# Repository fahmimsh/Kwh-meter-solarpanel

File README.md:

# Kwh-meter-solarpanel

STM32F103C8T6

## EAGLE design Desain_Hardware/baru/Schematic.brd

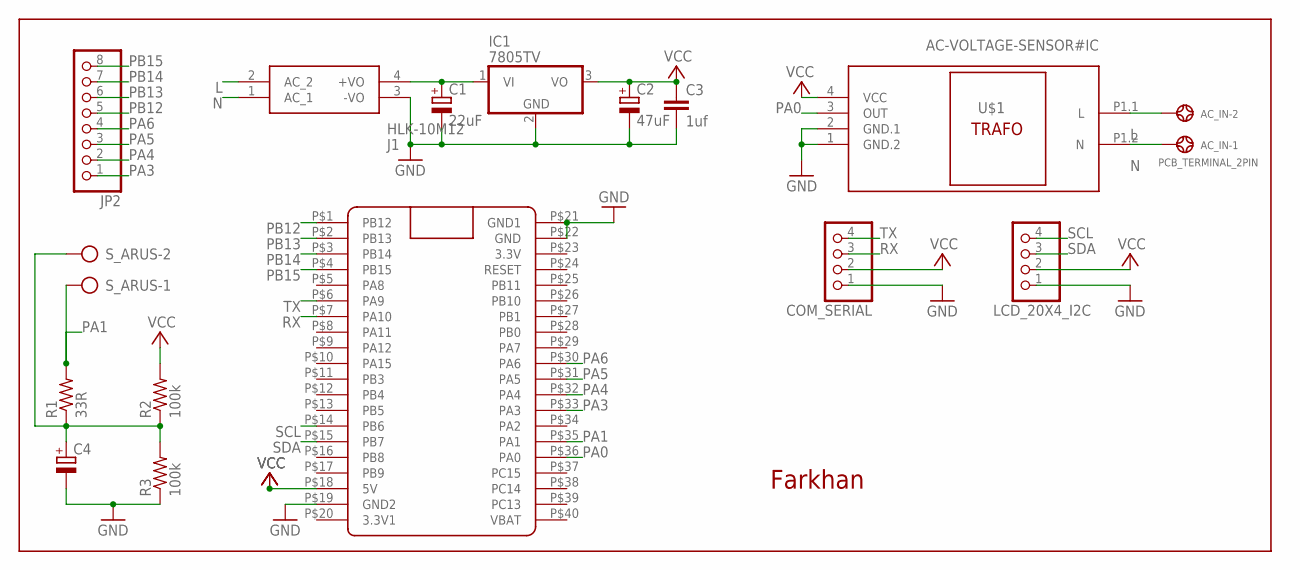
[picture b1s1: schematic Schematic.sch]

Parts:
AC_IN: PCB_TERMINAL_2PIN
C1: 22uF; E2,5-7
C2: 47uF; E2,5-7
C3: 1uf; C050-025X075
C4: CPOL-EUE2.5-6; E2,5-6
COM_SERIAL: PINHD-1X4; 1X04
IC1: 7805TV; TO220V
J1: HLK-10M12; HLK10M12
JP2: PINHD-1X8; 1X08
LCD_20X4_I2C: PINHD-1X4; 1X04
R1: 33R; 0207/10
R2, R3: 100k; 0207/10
S_ARUS: AK500/2
U$1: AC-VOLTAGE-SENSOR#IC
U$2: BLUE_PILL

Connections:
GND: C1.-, C2.-, C3.2, C4.-, COM_SERIAL.1, IC1.2 (GND), J1.3 (-VO), LCD_20X4_I2C.1, R3.1, U$1.1 (GND.2), U$1.2 (GND.1), U$2.P$19 (GND2), U$2.P$21 (GND1), U$2.P$22 (GND)
L: AC_IN.2, J1.2 (AC_2), U$1.P1.1 (L)
N: AC_IN.1, J1.1 (AC_1), U$1.P1.2 (N)
unnamed: C1.+, IC1.1 (VI), J1.4 (+VO)
unnamed: C4.+, R1.1, R2.1, R3.2, S_ARUS.2
PA0: U$1.3 (OUT), U$2.P$36 (PA0)
PA1: R1.2, S_ARUS.1, U$2.P$35 (PA1)
PA3: JP2.1, U$2.P$33 (PA3)
PA4: JP2.2, U$2.P$32 (PA4)
PA5: JP2.3, U$2.P$31 (PA5)
PA6: JP2.4, U$2.P$30 (PA6)
PB12: JP2.5, U$2.P$1 (PB12)
PB13: JP2.6, U$2.P$2 (PB13)
PB14: JP2.7, U$2.P$3 (PB14)
PB15: JP2.8, U$2.P$4 (PB15)
RX: COM_SERIAL.3, U$2.P$7 (PA10)
SCL: LCD_20X4_I2C.4, U$2.P$14 (PB6)
SDA: LCD_20X4_I2C.3, U$2.P$15 (PB7)
TX: COM_SERIAL.4, U$2.P$6 (PA9)
VCC: C2.+, C3.1, COM_SERIAL.2, IC1.3 (VO), LCD_20X4_I2C.2, R2.2, U$1.4 (VCC), U$2.P$18 (5V)

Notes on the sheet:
Farkhan

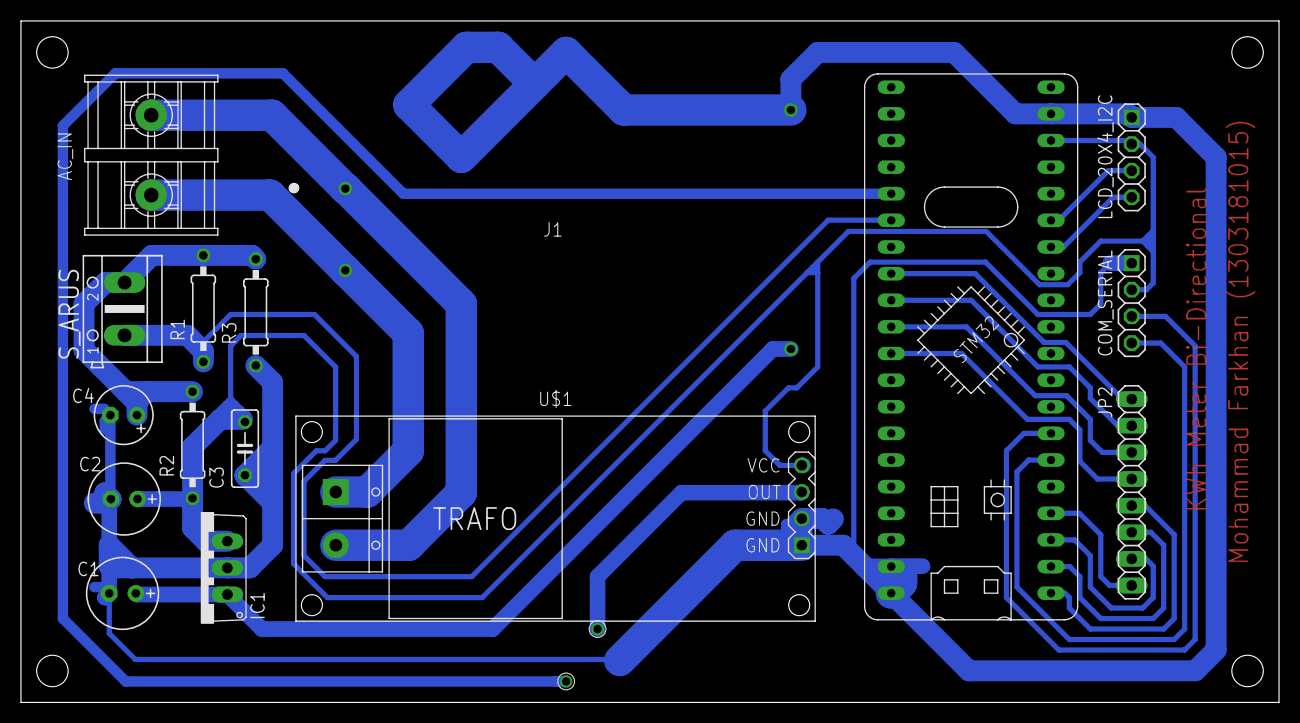
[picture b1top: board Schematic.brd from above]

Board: 2 copper layers, 120.0 x 65.0 mm, 16 parts (0 on the bottom side), 20 nets.

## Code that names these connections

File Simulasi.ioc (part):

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PD1-OSC_OUT.Mode=HSE-External-Oscillator
PA10.Mode=Asynchronous
Mcu.UserName=STM32F103C8Tx
PC13-TAMPER-RTC.Signal=GPIO_Output
PD0-OSC_IN.Signal=RCC_OSC_IN
PB13.Signal=GPIO_Output
PB15.Signal=GPIO_Output
RCC.SYSCLKSource=RCC_SYSCLKSOURCE_PLLCLK
PA0-WKUP.Signal=ADCx_IN0
PD1-OSC_OUT.Signal=RCC_OSC_OUT
PA13.Signal=SYS_JTMS-SWDIO
PA9.Mode=Asynchronous
PA9.Signal=USART1_TX
PB6.Signal=I2C1_SCL
PB6.Mode=I2C
PA1.Signal=ADCx_IN1
PD0-OSC_IN.Mode=HSE-External-Oscillator
PB14.Signal=GPIO_Output
PA5.Signal=GPIO_Input
board=custom
PA14.Mode=Serial_Wire
PB7.Signal=I2C1_SDA
PA13.Mode=Serial_Wire
Mcu.Name=STM32F103C(8-B)Tx
PA4.Signal=GPIO_Input
RCC.SYSCLKFreq_VALUE=72000000
Mcu.Package=LQFP48
PA6.Signal=GPIO_Input
PB7.Mode=I2C
PA10.Signal=USART1_RX
PA14.Signal=SYS_JTCK-SWCLK
PB12.Signal=GPIO_Output
PA3.Signal=GPIO_Input

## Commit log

2021-05-05 pjkelin
2021-07-23 terbaru

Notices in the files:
parts and their libraries:
diy-modules: Released under the Creative Commons Attribution 4.0 International License: http://creativecommons.org/licenses/by/4.0
SparkFun-Aesthetics: Licensing: Creative Commons ShareAlike 4.0 International - https://creativecommons.org/licenses/by-sa/4.0
